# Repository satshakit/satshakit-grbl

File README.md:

<div align="center"><h1 style="font-family: courier;" align="center">satshakit-grbl</h1></div>
<div align="center"></div>
<div align="center"><i>An open source & fabbable GRBL controller board.</i></div>

satshakit-grbl
--
satshakit-grbl is a microcontroller board designed to work with **[grbl](https://github.com/gnea/grbl/wiki)** that you can make in any Fab Lab. This board comes in two different versions, **serial** having integrated an usb port and a serial converter, and **noserial** for a bare metal grbl board. In both cases these boards will allow you to easily make your own machine controller for any kind of machine supported by grbl.

Here the **features** of the satshakit-grbl:

- **Atmega328p** for maximum compatibility with grbl
- **CH340G** and **USB** (serial version)
- **USB programming** and **serial communication** (serial version)
- **endstop noise filtering**
- logically disposed **grbl pinout**
- 2.54mm pitch **wire to board connectors** compatibility
- **multiple GNDs and VCCs** to connect all the required drivers/switches
- cost of about **4€** (serial version)

Here are the schematic and the board of the **serial** version:

And here the schematic and the board of the **noserial** version:

downloads
--

- **[satshakit-grbl serial schematic](https://github.com/satshakit/satshakit-grbl/raw/master/eagle/serial/satshakit-grbl.sch)**
- **[satshakit-grbl serial board](https://github.com/satshakit/satshakit-grbl/raw/master/eagle/serial/satshakit-grbl.brd)**
- **[satshakit-grbl serial internal png](https://github.com/satshakit/satshakit-grbl/raw/master/media/internal_s.png)**
- **[satshakit-grbl serial external png](https://github.com/satshakit/satshakit-grbl/raw/master/media/external_s.png)**

- **[satshakit-grbl noserial schematic](https://github.com/satshakit/satshakit-grbl/raw/master/eagle/no_serial/satshakit-grbl.sch)**
- **[satshakit-grbl noserial board](https://github.com/satshakit/satshakit-grbl/raw/master/eagle/no_serial/satshakit-grbl.brd)**
- **[satshakit-grbl noserial internal png](https://github.com/satshakit/satshakit-grbl/raw/master/media/internal_ns.png)**
- **[satshakit-grbl noserial external png](https://github.com/satshakit/satshakit-grbl/raw/master/media/external_ns.png)**

- **[satshakit-grbl BOM xlsx](https://github.com/satshakit/satshakit-grbl/raw/master/bom/satshakit-grbl-bom.xlsx)**
- **[satshakit-grbl BOM ods](https://github.com/satshakit/satshakit-grbl/raw/master/bom/satshakit-grbl-bom.ods)**

getting started
--

Before using a satshakit-grbl board on your machine, it is necessary to **upload the grbl**. In both version is recommeded to first upload the **Arduino bootloader** using an ISP programmer. Here is an example using **[Arduino as ISP](https://www.arduino.cc/en/Tutorial/ArduinoISP)** for both versions. More info are available in the **[satshakit repository](https://github.com/satshakit/satshakit)**.

After having uploaded the Arduino bootloader, it is possible to directly upload the grbl using a **mini USB cable** for the **serial version**, or an **FTDI cable** for the **noserial** version. Find here a schema on how to connect the noserial version with an FTDI cable:

Finally, to **connect your satshakit-grbl to your machine**, here the **pinouts** of both versions:

media
--

**images:**

**videos:**

License
--
This work is licensed under the terms of the open source license: Creative Commons Attribution-ShareAlike 4.0 International ([CC BY-SA 4.0](https://creativecommons.org/licenses/by-sa/4.0/)).

Disclaimer  
--

<div class="align-justify">
This hardware/software is provided "as is", and you use the hardware/software at your own risk. Under no circumstances shall any author be liable for direct, indirect, special, incidental, or consequential damages resulting from the use, misuse, or inability to use this hardware/software, even if the authors have been advised of the possibility of such damages.</div>

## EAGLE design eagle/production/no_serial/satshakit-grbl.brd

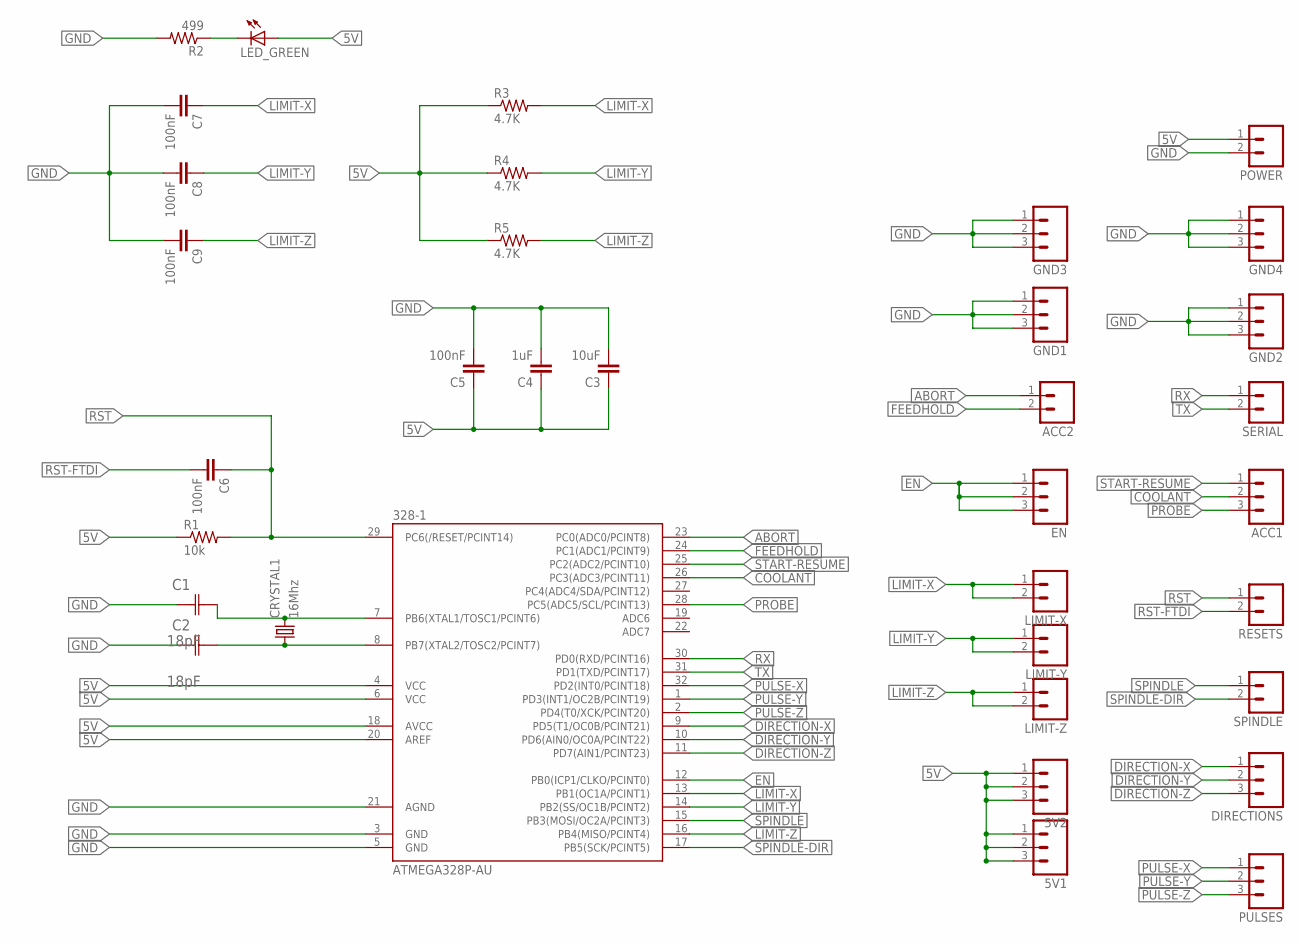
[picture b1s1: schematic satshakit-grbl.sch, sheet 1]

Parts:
5V1, 5V2: M03; 03P
328-1: ATMEGA328P-AU; TQFP32-08
ACC1: M03; 03P
ACC2: M02; 02P
C1, C2: 18pF; CAPC3216X178N
C3: 10uF; 1206
C4: 1uF; 1206
C5, C6, C7, C8, C9: 100nF; 1206
CRYSTAL1: 16Mhz; CSM-7X-DU
DIRECTIONS: M03; 03P
EN: M03; 03P
GND1, GND2, GND3, GND4: M03; 03P
LED_GREEN: LED1206; 1206
LIMIT-X: M02; 02P
LIMIT-Y: M02; 02P
LIMIT-Z: M02; 02P
POWER: M02; 02P
PULSES: M03; 03P
R1: 10k; 1206
R2: 499; 1206
R3, R4, R5: 4.7K; 1206
RESETS: M02; 02P
SERIAL: M02; 02P
SPINDLE: M02; 02P

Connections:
5V: 5V1.1, 5V1.2, 5V1.3, 5V2.1, 5V2.2, 5V2.3, 328-1.4 (VCC), 328-1.6 (VCC), 328-1.18 (AVCC), 328-1.20 (AREF), C3.1, C4.1, C5.1, LED_GREEN.1 (A), POWER.1, R1.1, R3.1, R4.1, R5.1
ABORT: 328-1.23 (PC0(ADC0/PCINT8)), ACC2.1
COOLANT: 328-1.26 (PC3(ADC3/PCINT11)), ACC1.2
DIRECTION-X: 328-1.9 (PD5(T1/OC0B/PCINT21)), DIRECTIONS.1
DIRECTION-Y: 328-1.10 (PD6(AIN0/OC0A/PCINT22)), DIRECTIONS.2
DIRECTION-Z: 328-1.11 (PD7(AIN1/PCINT23)), DIRECTIONS.3
EN: 328-1.12 (PB0(ICP1/CLKO/PCINT0)), EN.1, EN.2, EN.3
FEEDHOLD: 328-1.24 (PC1(ADC1/PCINT9)), ACC2.2
GND: 328-1.3 (GND), 328-1.5 (GND), 328-1.21 (AGND), C1.1 (C1), C2.1 (C1), C3.2, C4.2, C5.2, C7.2, C8.2, C9.2, GND1.1, GND1.2, GND1.3, GND2.1, GND2.2, GND2.3, GND3.1, GND3.2, GND3.3, GND4.1, GND4.2, GND4.3, POWER.2, R2.2
LIMIT-X: 328-1.13 (PB1(OC1A/PCINT1)), C7.1, LIMIT-X.1, LIMIT-X.2, R3.2
LIMIT-Y: 328-1.14 (PB2(SS/OC1B/PCINT2)), C8.1, LIMIT-Y.1, LIMIT-Y.2, R4.2
LIMIT-Z: 328-1.16 (PB4(MISO/PCINT4)), C9.1, LIMIT-Z.1, LIMIT-Z.2, R5.2
unnamed: 328-1.7 (PB6(XTAL1/TOSC1/PCINT6)), C1.2 (C2), CRYSTAL1.2
unnamed: 328-1.8 (PB7(XTAL2/TOSC2/PCINT7)), C2.2 (C2), CRYSTAL1.1
unnamed: LED_GREEN.2 (C), R2.1
PROBE: 328-1.28 (PC5(ADC5/SCL/PCINT13)), ACC1.3
PULSE-X: 328-1.32 (PD2(INT0/PCINT18)), PULSES.1
PULSE-Y: 328-1.1 (PD3(INT1/OC2B/PCINT19)), PULSES.2
PULSE-Z: 328-1.2 (PD4(T0/XCK/PCINT20)), PULSES.3
RST: 328-1.29 (PC6(/RESET/PCINT14)), C6.1, R1.2, RESETS.1
RST-FTDI: C6.2, RESETS.2
RX: 328-1.30 (PD0(RXD/PCINT16)), SERIAL.1
SPINDLE: 328-1.15 (PB3(MOSI/OC2A/PCINT3)), SPINDLE.1
SPINDLE-DIR: 328-1.17 (PB5(SCK/PCINT5)), SPINDLE.2
START-RESUME: 328-1.25 (PC2(ADC2/PCINT10)), ACC1.1
TX: 328-1.31 (PD1(TXD/PCINT17)), SERIAL.2

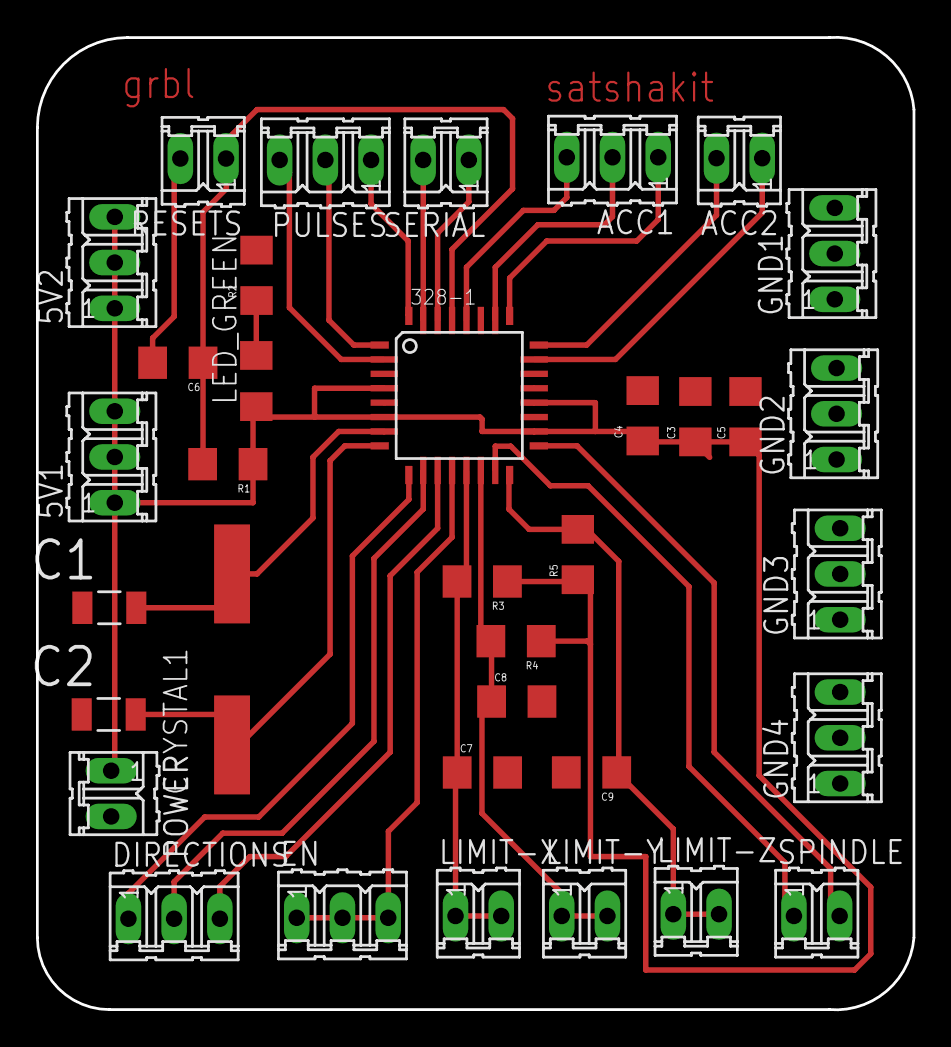
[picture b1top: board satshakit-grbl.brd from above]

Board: 2 copper layers, 48.7 x 54.0 mm, 35 parts (0 on the bottom side), 26 nets.

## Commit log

2018-04-28 updated designs
2018-04-28 updated images
2018-04-28 added milling images
2018-05-01 added pinouts
2018-05-01 added programming images
2018-05-01 added readme info
2018-05-01 added BOM
2018-05-01 added media
2018-05-01 readme fixes
2018-05-02 added production pcbs
2018-05-02 added picture
2020-05-31 license change

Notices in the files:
parts and their libraries:
01_SparkFun: Licensing: CC v3.0 Share-Alike You are welcome to use this library for commercial purposes.
SparkFun-DigitalIC: Licensing: Creative Commons ShareAlike 4.0 International - https://creativecommons.org/licenses/by-sa/4.0
